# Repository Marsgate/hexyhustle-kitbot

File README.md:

# Hexy Hustle Kit Bot
This repository contains the CAD, code, and assembly instructions necessary to build a Hexy Hustle Kit Bot.

## Printing
Printable STLs have been provided for all kit bot parts in the STL folder. Check the BOM for quantity to print.

All kits are printed on Bambu Labs 0.20mm Standard settings. 

## Standard Hardware
Kitbots utilize the following standard hardware
- 4mm Round Shafts
- 5mm Hex Shafts
- M3 Socket Head Screws
- M3 Heatset Inserts

When designing 3D printable parts to interface with this hardware, the following dimensions tend to work well.
- 0.13", M3 screw thru hole diameter for hole printed flat
- 0.14", M3 screw thru hole diameter for hold printed standing up
- 0.15", Counterbore depth for M3 socket screws 
- 0.18", M3 Heatset insert hole diameter
- 0.115", M3 hole diameter for threading into the plastic when printed flat
- 0.108", M3 hole diameter for threading into the plastic when printed standing up
- 0.25", 5mm Hex shaft thru hole diameter
- 0.2", Blind depth of a heatset insert hole
- 0.18", 4mm Shaft thru hole diameter

Holes printed standing up are smaller to accounts for drooping during printing. This may vary from printer to printer depending on overhang performance.

## Assembly
If you did not buy a kit that contains all prints, start by printing the STLs contained in CAD/Kitbot. Reference the BOM.md to see quantities of each part to print. If a part is mirrored, a pre-mirrored STL is provided for convenience.

Assembly video coming soon!

## Lipo charging
Do not leave batteries unattended while charging! 
It is reccommended that you charge batteries in a lipo safe bag/box.

B6 Neo manual:
https://www.skyrc.com/download/100198%20B6neo%20Instruction%20Manual%20V1.1_240318.pdf

After using the batteries, it is reccommended to discharge them to storage voltage for longevity.

## Code

### Setup

1. Install the Arduino IDE https://www.arduino.cc/en/software/
2. Add the ESP32 and Bluepad32 board packages to Board Manager
- [Video Tutorial](https://www.youtube.com/watch?v=0jnY-XXiD8Q) (You do not need to open the example project)
- Paste the following text into the "additional boards manager URLs" section per the instructions linked above.
 ```
 https://raw.githubusercontent.com/espressif/arduino-esp32/gh-pages/package_esp32_index.json
 https://raw.githubusercontent.com/ricardoquesada/esp32-arduino-lib-builder/master/bluepad32_files/package_esp32_bluepad32_index.json
 ```
- Install the esp32 and bluepad32 packages by clicking the "Install" button in the board manager.
3. Install the ESP32Servo library
4. Open the Code.ino file
5. Select the board "esp32_bluepad32 > ESP32 Dev Module"
6. Plug in the brain, and select the COM port that appears.
7. Verify that uploading code to the brain works

If the upload fails, try setting the baud rate to 115200 and retrying.

### Configuration

Define all motors and servos at the top of Code.ino
Here are the example definitions from the kitbot itself
```
// motors
Motor leftDrive;
Motor rightDrive;
Motor intake;
Motor hang;

// servos
ServoMotor flipper;
const int flipperMin = 500;
const int flipperMax = 2050;
```
Defining limits for the servo is helpful for writing driver controls. These should be values between 500 and 2500.

In the `setup()` function, assign motor and servo ports. DC motors can be reversed by adding `,1` after the port. Servos should be given a starting position that it moves to when the robot is turned on. This is usually the min or max value, but doesn't have to be.
```
// motors
leftDrive.init(M3); 
rightDrive.init(M4, 1); // reversed
intake.init(M6);
hang.init(M2);

// servos
flipper.init(S1, flipperMin);
```

### Driver Controls

In the `driverControls()` function, map controller buttons to subsystems
```
// intake
if (ctl->r1()) {
    intake.move(100);
} else if (ctl->r2()) {
    intake.move(-100);
} else {
    intake.move(0);
}
```
In this example, the intake runs forward when R1 is pressed, backwards when R2 is pressed, and stops when neither button is pressed.

For the chassis controls, they are configured for split arcade by default.
```
leftDrive.move(y-x);
rightDrive.move(y+x);
```

#### Split Arcard
Get the joystick values from the same stick, instead of two different sticks.
```
// left stick
int x = ctl->axisX();
int y = ctl->axisY();
```
```
// right stick
int x = ctl->axisRX();
int y = ctl->axisRY();
```

#### Tank Drive
Switch from the RX axis to the RY axis.
```
// get joysticks
int x = ctl->axisRY();
int y = ctl->axisY();
```
Then update the left and right drive assignment to use the joystick values directly instead of adding/subtracting them.
```
leftDrive.move(y);
rightDrive.move(x);
```

## Attribution
Credit to Ricardo Quesada for creating the bluepad32 library that the Kitbot runs on
https://github.com/ricardoquesada/bluepad32

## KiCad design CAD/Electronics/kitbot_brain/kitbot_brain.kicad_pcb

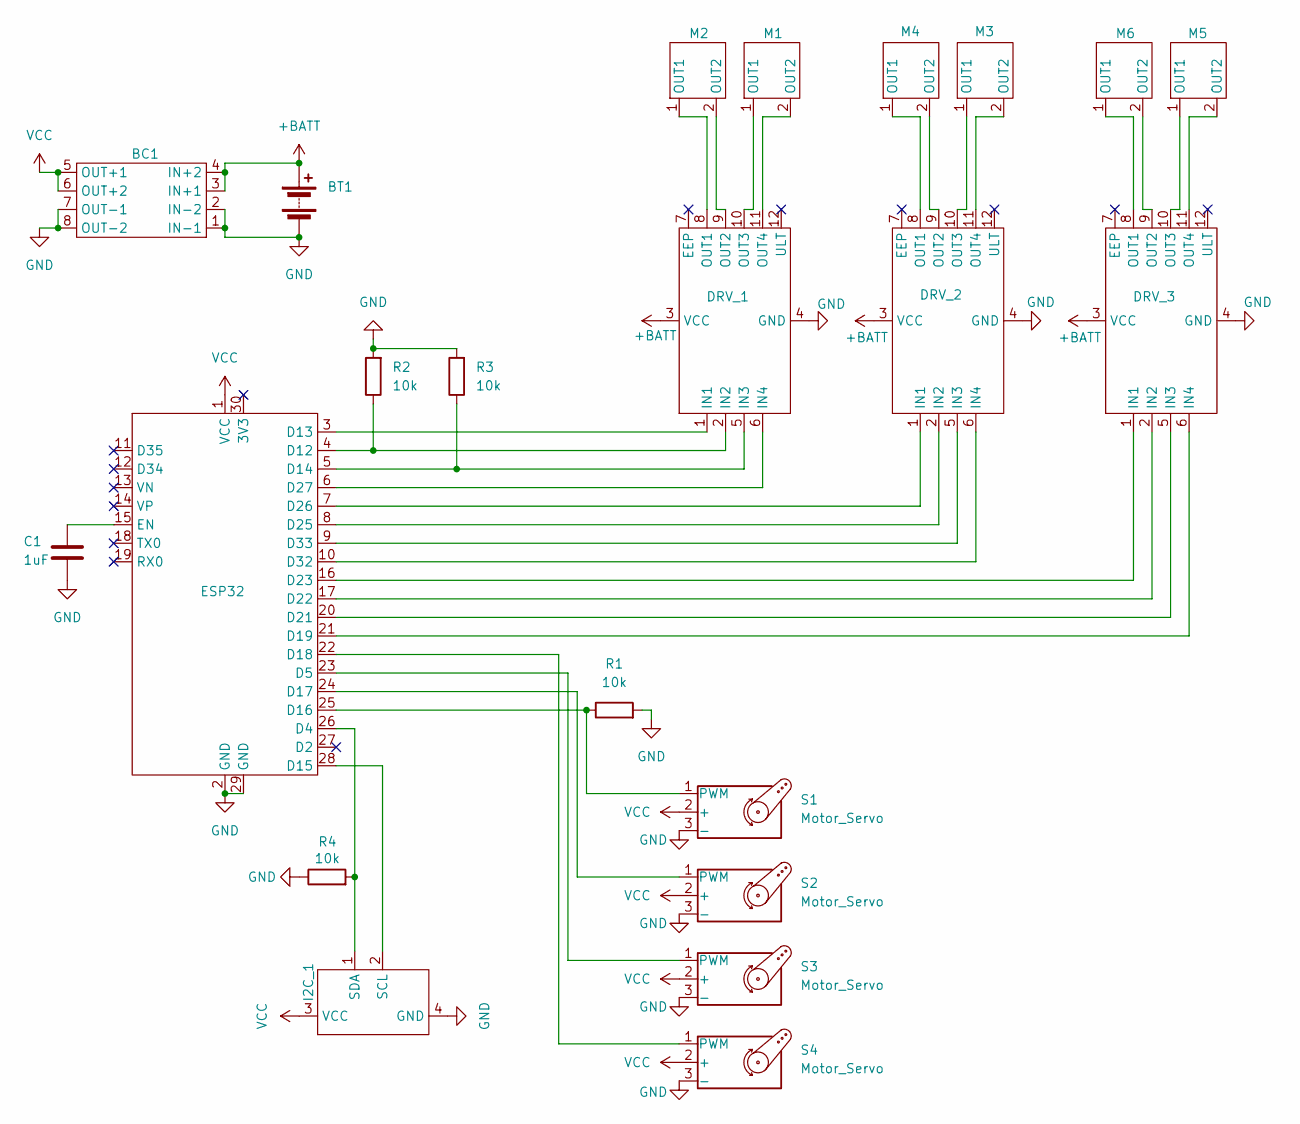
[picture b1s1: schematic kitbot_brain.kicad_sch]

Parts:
BC1: buck converter
BT1: Battery; AMASS_XT60PW-M_1x02_P7.20mm_Horizontal
C1: 1uF; C_1206_3216Metric_Pad1.33x1.80mm_HandSolder
DRV_1, DRV_2, DRV_3: drv8833
ESP32: ESP32
I2C_1: JST_XH_S4B-XH-A_1x04_P2.50mm_Horizontal
M1, M2, M3, M4, M5, M6: JST_XH_S2B-XH-A_1x02_P2.50mm_Horizontal
R1, R2, R3, R4: 10k; R_1206_3216Metric_Pad1.30x1.75mm_HandSolder
S1, S2, S3, S4: Motor_Servo; PinHeader_1x03_P2.54mm_Horizontal

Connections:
+BATT: BC1.3 (IN+1), BC1.4 (IN+2), BT1.1 (+), DRV_1.3 (VCC), DRV_2.3 (VCC), DRV_3.3 (VCC)
GND: BC1.1 (IN-1), BC1.2 (IN-2), BC1.7 (OUT-1), BC1.8 (OUT-2), BT1.2 (-), C1.2, DRV_1.4 (GND), DRV_2.4 (GND), DRV_3.4 (GND), ESP32.2 (GND), ESP32.29 (GND), I2C_1.4 (GND), R1.2, R2.2, R3.2, R4.1, S1.3 (-), S2.3 (-), S3.3 (-), S4.3 (-)
unnamed: DRV_1.1 (IN1), ESP32.3 (D13)
unnamed: DRV_1.2 (IN2), ESP32.4 (D12), R2.1
unnamed: DRV_1.5 (IN3), ESP32.5 (D14), R3.1
unnamed: DRV_1.6 (IN4), ESP32.6 (D27)
unnamed: DRV_1.8 (OUT1), M2.1 (OUT1)
unnamed: DRV_1.9 (OUT2), M2.2 (OUT2)
unnamed: DRV_1.10 (OUT3), M1.1 (OUT1)
unnamed: DRV_1.11 (OUT4), M1.2 (OUT2)
unnamed: DRV_2.1 (IN1), ESP32.7 (D26)
unnamed: DRV_2.2 (IN2), ESP32.8 (D25)
unnamed: DRV_2.5 (IN3), ESP32.9 (D33)
unnamed: DRV_2.6 (IN4), ESP32.10 (D32)
unnamed: DRV_2.8 (OUT1), M4.1 (OUT1)
unnamed: DRV_2.9 (OUT2), M4.2 (OUT2)
unnamed: DRV_2.10 (OUT3), M3.1 (OUT1)
unnamed: DRV_2.11 (OUT4), M3.2 (OUT2)
unnamed: DRV_3.1 (IN1), ESP32.16 (D23)
unnamed: DRV_3.2 (IN2), ESP32.17 (D22)
unnamed: DRV_3.5 (IN3), ESP32.20 (D21)
unnamed: DRV_3.6 (IN4), ESP32.21 (D19)
unnamed: DRV_3.8 (OUT1), M6.1 (OUT1)
unnamed: DRV_3.9 (OUT2), M6.2 (OUT2)
unnamed: DRV_3.10 (OUT3), M5.1 (OUT1)
unnamed: DRV_3.11 (OUT4), M5.2 (OUT2)
unnamed: ESP32.26 (D4), I2C_1.1 (SDA), R4.2
unnamed: ESP32.23 (D5), S3.1 (PWM)
unnamed: ESP32.28 (D15), I2C_1.2 (SCL)
unnamed: ESP32.25 (D16), R1.1, S1.1 (PWM)
unnamed: ESP32.24 (D17), S2.1 (PWM)
unnamed: ESP32.22 (D18), S4.1 (PWM)
unnamed: C1.1, ESP32.15 (EN)
VCC: BC1.5 (OUT+1), BC1.6 (OUT+2), ESP32.1 (VCC), I2C_1.3 (VCC), S1.2 (+), S2.2 (+), S3.2 (+), S4.2 (+)

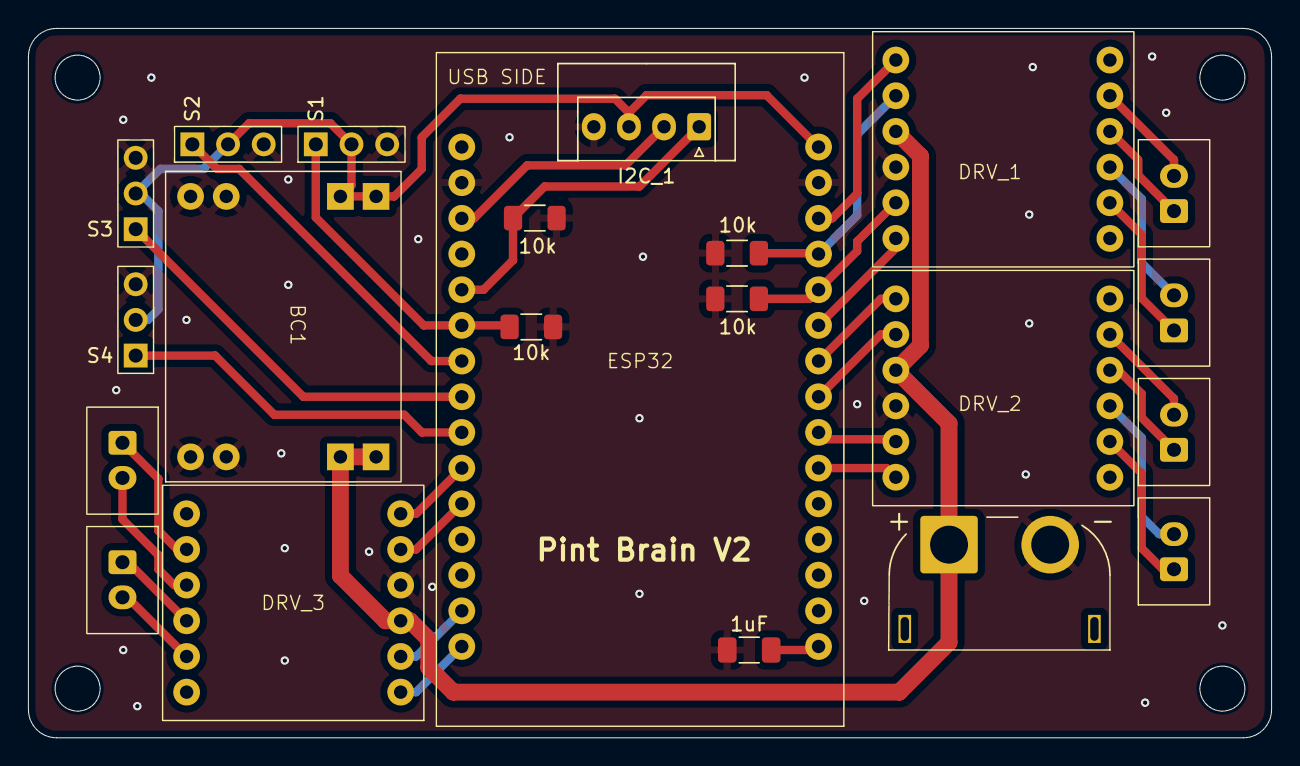
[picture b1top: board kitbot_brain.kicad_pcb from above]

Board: 2 copper layers, 88.5 x 50.5 mm, 22 parts (0 on the bottom side), 34 nets.

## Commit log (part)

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2025-09-20 Add existing code
2025-09-20 Add STLs for emergency reprints
2025-10-12 Add gitignore
2025-10-20 Turn on the onboard LED on disconnect
2025-10-20 Use boot button to put board into pairing mode
2025-10-23 Move remaining logic to library
2025-10-30 Haunted Hustle pre-comp tuning
2025-10-31 Fix ESC initialization beeping
2026-04-03 Kit Bot
2026-05-15 Tune flipper angle
2026-05-18 Update port names
2026-05-26 Add STLs
2026-05-26 Update readme and reorganize project
2026-05-26 Update BOM
2026-05-26 Update traction wheel STL
2026-05-28 Fix Intake tower motor mount holes
2026-05-29 Fix m3 hole tolerance
2026-06-03 Updates after building Nathan's bot
2026-06-03 More updates based on build feedback
2026-06-03 Add full bot plate
2026-06-14 Update tower STLs
2026-06-14 Add extension cables to BOM
2026-06-16 Add links to BOM
2026-06-16 Add individual omni STLs
2026-06-16 Put hang on L2
2026-06-16 Split arcade default
2026-06-21 Increase case counterbore
